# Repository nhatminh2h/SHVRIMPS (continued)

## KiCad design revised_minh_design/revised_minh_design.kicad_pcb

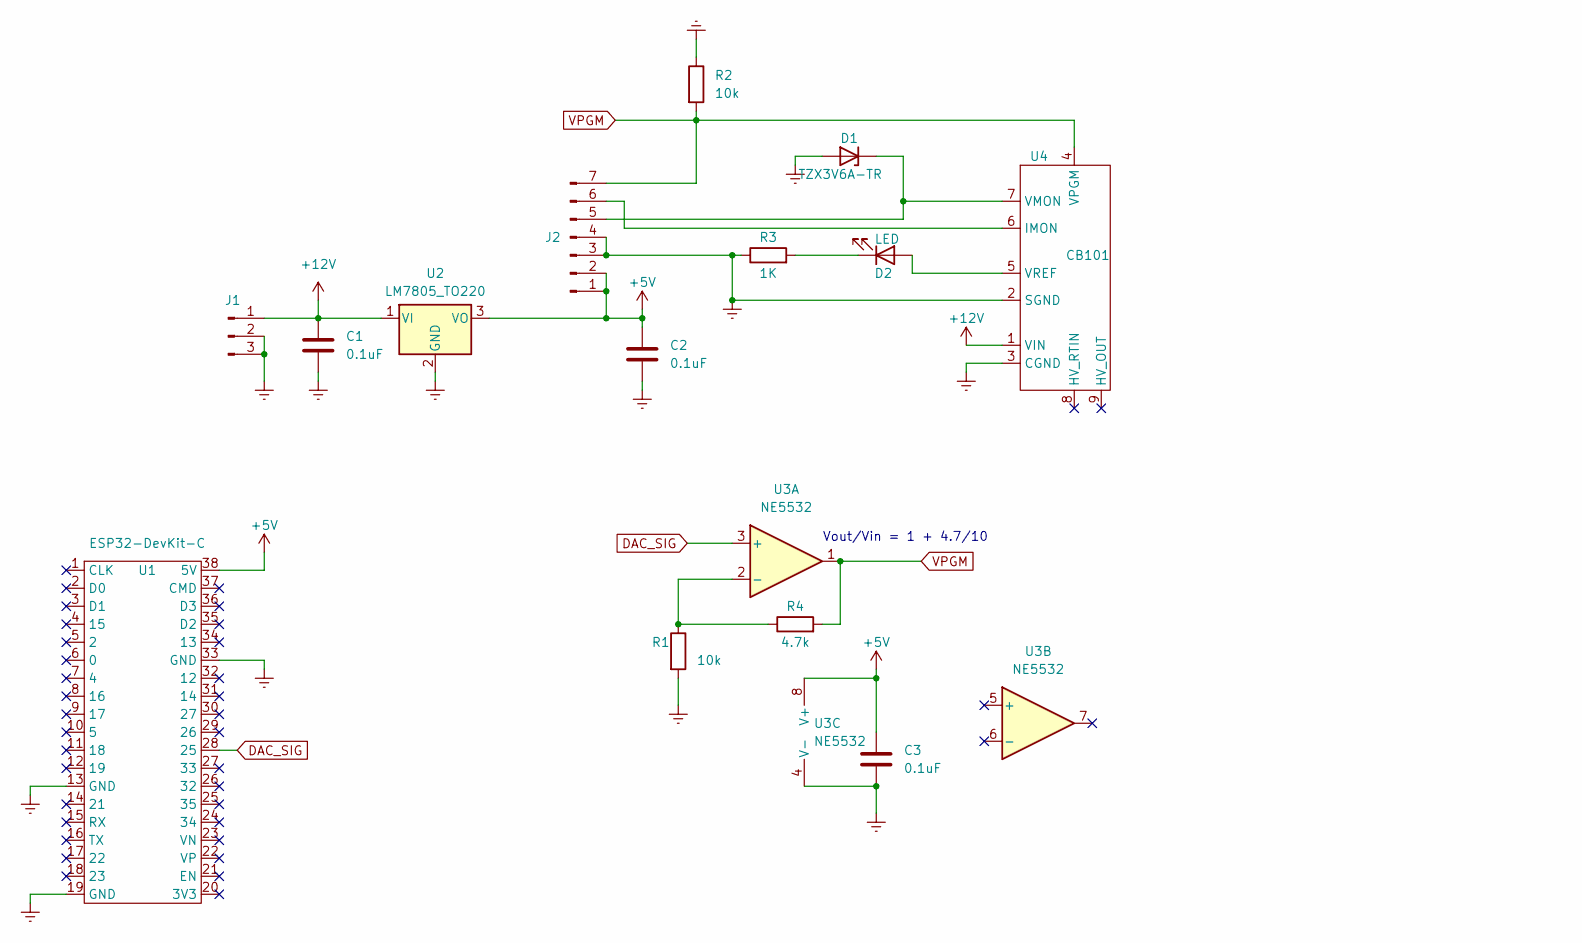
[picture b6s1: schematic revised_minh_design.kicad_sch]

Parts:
C1, C2, C3: 0.1uF; C_Disc_D6.0mm_W2.5mm_P5.00mm
D1: TZX3V6A-TR; D_DO-35_SOD27_P7.62mm_Horizontal
D2: LED; LED_D3.0mm_Clear
J1: Conn_01x03_Male; PinSocket_1x03_P2.54mm_Vertical
J2: Conn_01x07_Male; PinSocket_1x07_P2.54mm_Vertical
R1, R2: 10k; R_Axial_DIN0309_L9.0mm_D3.2mm_P15.24mm_Horizontal
R3: 1K; R_Axial_DIN0309_L9.0mm_D3.2mm_P15.24mm_Horizontal
R4: 4.7k; R_Axial_DIN0309_L9.0mm_D3.2mm_P15.24mm_Horizontal
U1: ESP32-DevKit-C; ESP32-devkitC-v4
U2: LM7805_TO220; TO-220-3_Vertical
U3: NE5532; DIP-8_W7.62mm
U4: CB101

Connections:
+5V: C2.1, C3.1, J2.1, J2.2, U1.38 (5V), U2.3 (VO), U3.8 (V+)
+12V: C1.1, J1.1, U2.1 (VI), U4.1 (VIN)
DAC_SIG: U1.28 (25), U3.3 (+)
Earth: C1.2, C2.2, C3.2, D1.2 (A), J1.2, J1.3, J2.3, J2.4, R1.2, R2.1, R3.1, U1.13 (GND), U1.19 (GND), U1.33 (GND), U2.2 (GND), U3.4 (V-), U4.2 (SGND), U4.3 (CGND)
unnamed: D1.1 (K), J2.5, U4.7 (VMON)
unnamed: D2.1 (K), R3.2
unnamed: D2.2 (A), U4.5 (VREF)
unnamed: J2.6, U4.6 (IMON)
unnamed: R1.1, R4.1, U3.2 (-)
VPGM: J2.7, R2.2, R4.2, U3.1, U4.4 (VPGM)

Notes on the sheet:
Vout/Vin = 1 + 4.7/10

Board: 2 copper layers, 15 parts (0 on the bottom side), 10 nets, no tracks yet.

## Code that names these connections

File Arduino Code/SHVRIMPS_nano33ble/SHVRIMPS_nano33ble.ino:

#include <dac8568.h>
#include <MCP346X.h>
#include <SPI.h>

//********************** ESP 32 Pin *******************//
//const int DAC_CS = ; //4
//const int LDAC = //17
//const int CLR //16

//const int ADC1_CS = ; //33
//const int ADC2_CS = ; //32
//const int ADC_MDAT = ; //35



//********************** NANO33 BLE Pin ***************//
const int DAC_CS = 2; //D2
const int LDAC = 4; //D4
const int CLR = 3;//D3
const int SCKL = 13; //D13

const int ADC1_CS = 6; //A2
const int ADC2_CS = 5; //A1
const int ADC_MDAT = 4; //A0

SPISettings DACsettings(2000000, MSBFIRST, SPI_MODE1); //2 mhz

uint32_t messagetoDAC;

void writetoDAC(uint32_t message){
  Serial.println("tick");
  digitalWrite(DAC_CS, LOW);
  SPI.beginTransaction(DACsettings);
  SPI.transfer(message >> 24);
  SPI.transfer(message >> 16);
  SPI.transfer(message >> 8);
  SPI.transfer(message);
  //SPI.transfer(&message,4);
  SPI.endTransaction();
  digitalWrite(DAC_CS, HIGH);
}

void setup() {
  //setting up SPI
  delay(2000);
  SPI.begin();
  
  //creating one ADC
  //MCP346X ADC1(ADC1_CS, ADC_MDAT);
  //writing to config registers
  //ADC1.setConfig0(ADC1.CLK_INTERNAL, ADC1.CS_NONE, ADC1.ADC_MODE_CONV);
  //ADC1.setConfig1(ADC1.MCLK_1, ADC1.OSR_256);
  //ADC1.setConfig2(ADC1.CH_I_1, ADC1.GAIN_1, ADC1.AZ_MUX_OFF);
  //ADC1.setConfig3(ADC1.CONV_CONTINUOUS, ADC1.DATA_FORM_32B_SID, ADC1.CRC_FORM_16B, ADC1.CRC_COM_OFF, ADC1.OFFCAL_OFF, ADC1.GAINCAL_OFF);
  //ADC1.setIRQ(ADC1.IRQ_PIN_IRQ, ADC1.IRQ_PINMODE_PP, ADC1.FASTCMD_ON, ADC1.EN_STP_ON);
  //creating DAC
  pinMode(DAC_CS, OUTPUT);
  digitalWrite(DAC_CS, HIGH);
  delay(100);

  pinMode(LDAC, OUTPUT);
  digitalWrite(LDAC, LOW);
  
  messagetoDAC = DAC8568_Setup(CONTROL_SETUP_FLEX_MODE, DATA_POWER_UP_INT_REF_ALWAYS_FLEX, FEATURE_POWER_UP_INT_REF_ALWAYS_FLEX);
  //messagetoDAC = 0b0000100100001010000000000000000;
  writetoDAC(messagetoDAC);
  delay(10);

  Serial.begin(9600);
}

void loop() {
  //messagetoDAC = 0b0000100100001010000000000000000;
  //writetoDAC(messagetoDAC);
  //delay(2000);

  
  messagetoDAC = DAC8568_Write_Input_Reg_And_Update_Single(BROADCAST,65535/15*1);
  //messagetoDAC = 0b00000010111111111111111111110000;

  Serial.println(messagetoDAC, HEX);
  writetoDAC(messagetoDAC);
  delay(5000);


  messagetoDAC = 0b00000010000000000000000000000000;
  messagetoDAC = DAC8568_Write_Input_Reg_And_Update_All(BROADCAST,0);
  Serial.println(messagetoDAC, HEX);
  writetoDAC(messagetoDAC);
  delay(5000);
}

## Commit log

2022-06-17 altium to kicad schematics
2022-06-18 libraries and footprints
2022-06-18 separated
2022-06-19 ADC_DAC
2022-06-22 HV Module routed, some footprint changes
2022-06-22 components routing mostly finished for DAC/ADC board
2022-06-22 minor adjustments
2022-06-23 resolved DRC errors and most warnings
2022-06-23 DAC ground to AGND, new AGND polygon pour
2022-06-24 Split ground plane design with no errors
2022-06-24 Fab ready version with joined ground plane, extra caps for ADCs
2022-06-24 Repositioned clock closer
2022-06-25 JLCPB Submission. Name added, connectors changed to double layer
2022-06-25 JLCPB Submission. Name added, connectors changed to double layer, rounded corners
2022-06-25 Added NANO33 BLE footprint, and stiching vias near mcu
2022-06-25 JLCPCB submission for dual MCU design
2022-06-28 New HV board for 15A12
2022-06-28 JLCPCB Submission for 15A12 board
2022-06-29 JLCPCB Submission for 15A12 board, double row connectors added, separate power and signal connectors
2022-06-29 new diagrams and adapter board
2022-06-29 adapter board 4 layers
2022-07-10 exported STEP file. Minor changes to schematics for better documentations
2022-09-20 reordering files, added plotting web plotting stuff
2022-09-22 DAC software arduino
2022-09-22 further DAC setup arduino code
2022-09-24 Fixed PI PO, DAC port ordering, MDAT Pin, clock connection
2022-09-24 moved from master to main
2022-09-24 cleanup
2022-09-24 Used 2nd opamp for unity gain on VMON
2022-09-24 routed the netlist for ADC/DAC v2
2022-09-25 software update, added some diagrams
2022-09-25 added BOM Excel
2022-09-26 renamed file and added requirements
2022-09-26 updated requirements, added serial streaming
2022-09-27 LUTs and diagrams
2022-09-27 Added video s for Undulating Motion
2022-10-01 added horizontal videos, edited BOM
2022-10-01 edit demo video
2022-10-01 edited videos, updated BOM, added Matlab plots
2022-10-07 Added Graphical Abstract
2022-11-29 Checkpoint before big revamp
2022-12-03 hardware update to add GPIO directly to MCU
